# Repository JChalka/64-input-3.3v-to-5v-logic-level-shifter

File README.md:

# 64 input 3.3v to 5v logic level shifter
 Level shifter used to bring 3.3v logic to 5v logic using 4 SN74ALVC164245

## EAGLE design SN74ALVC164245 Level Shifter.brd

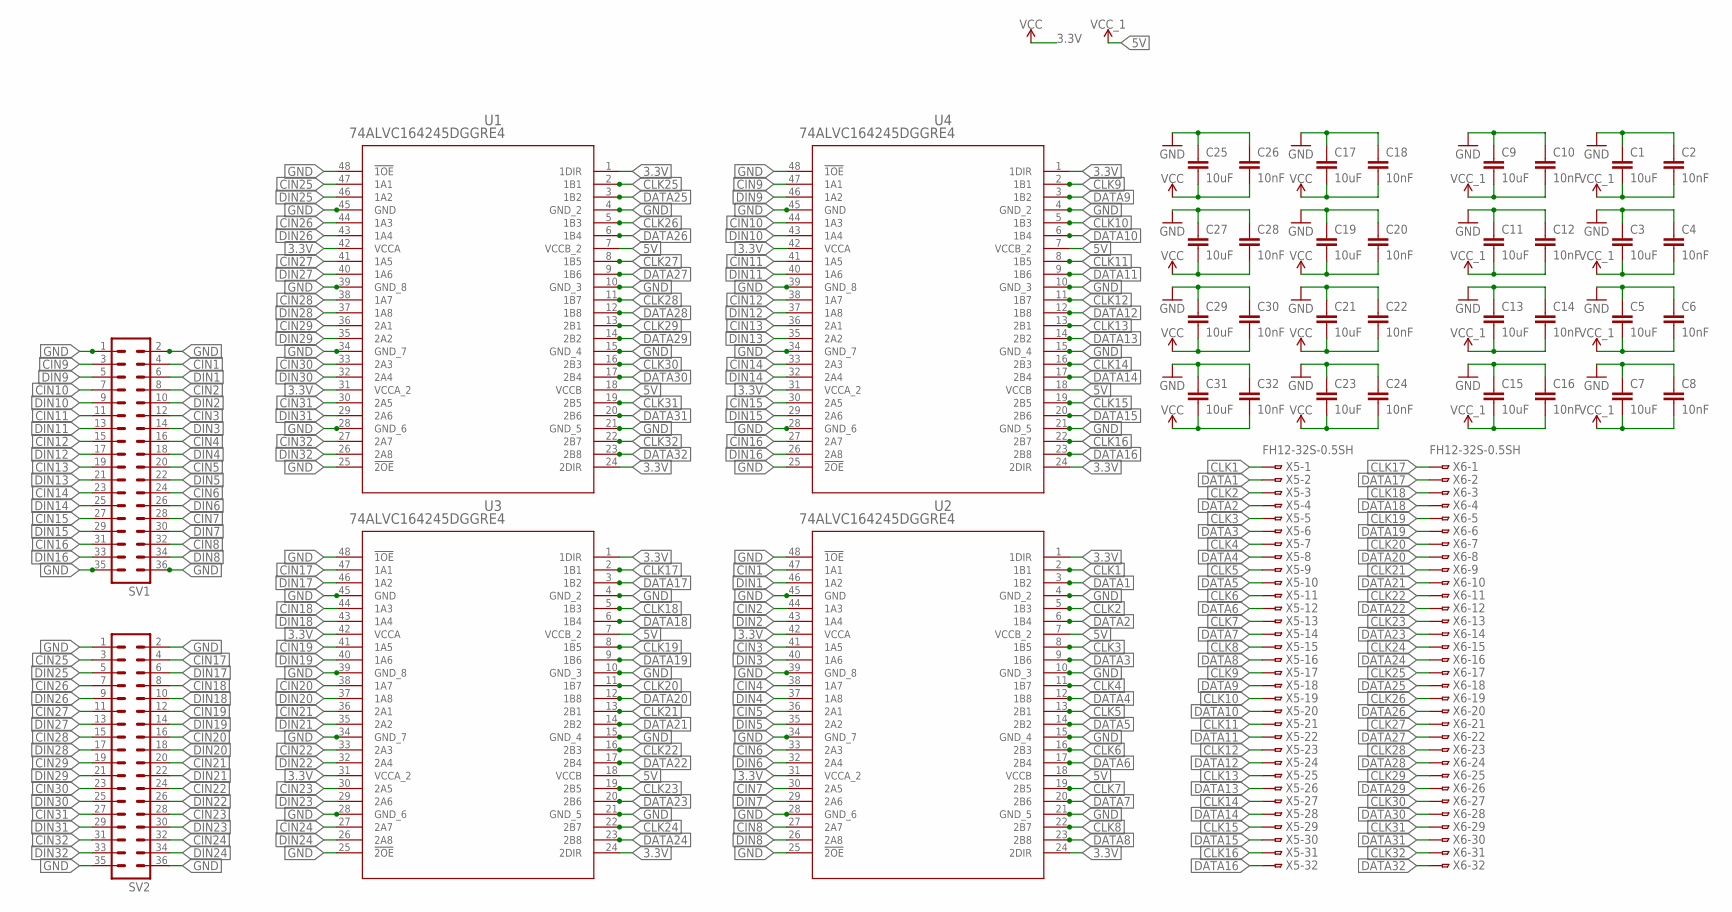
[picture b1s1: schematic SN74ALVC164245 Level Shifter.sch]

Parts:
C1, C3, C5, C7, C9, C11, C13, C15, C17, C19, C21, C23, C25, C27, C29, C31: 10uF; 0402-TIGHT
C2, C4, C6, C8, C10, C12, C14, C16, C18, C20, C22, C24, C26, C28, C30, C32: 10nF; 0402-TIGHT
SV1, SV2: MA18-2
U1, U2, U3, U4: 74ALVC164245DGGRE4; DGG48
X5, X6: FH12-32S-0.5SH

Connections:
3.3V: C17.2, C18.2, C19.2, C20.2, C21.2, C22.2, C23.2, C24.2, C25.2, C26.2, C27.2, C28.2, C29.2, C30.2, C31.2, C32.2, U1.1 (1DIR), U1.24 (2DIR), U1.31 (VCCA_2), U1.42 (VCCA), U2.1 (1DIR), U2.24 (2DIR), U2.31 (VCCA_2), U2.42 (VCCA), U3.1 (1DIR), U3.24 (2DIR), U3.31 (VCCA_2), U3.42 (VCCA), U4.1 (1DIR), U4.24 (2DIR), U4.31 (VCCA_2), U4.42 (VCCA)
5V: C1.2, C2.2, C3.2, C4.2, C5.2, C6.2, C7.2, C8.2, C9.2, C10.2, C11.2, C12.2, C13.2, C14.2, C15.2, C16.2, U1.7 (VCCB_2), U1.18 (VCCB), U2.7 (VCCB_2), U2.18 (VCCB), U3.7 (VCCB_2), U3.18 (VCCB), U4.7 (VCCB_2), U4.18 (VCCB)
CIN1: SV1.4, U2.47 (1A1)
CIN2: SV1.8, U2.44 (1A3)
CIN3: SV1.12, U2.41 (1A5)
CIN4: SV1.16, U2.38 (1A7)
CIN5: SV1.20, U2.36 (2A1)
CIN6: SV1.24, U2.33 (2A3)
CIN7: SV1.28, U2.30 (2A5)
CIN8: SV1.32, U2.27 (2A7)
CIN9: SV1.3, U4.47 (1A1)
CIN10: SV1.7, U4.44 (1A3)
CIN11: SV1.11, U4.41 (1A5)
CIN12: SV1.15, U4.38 (1A7)
CIN13: SV1.19, U4.36 (2A1)
CIN14: SV1.23, U4.33 (2A3)
CIN15: SV1.27, U4.30 (2A5)
CIN16: SV1.31, U4.27 (2A7)
CIN17: SV2.4, U3.47 (1A1)
CIN18: SV2.8, U3.44 (1A3)
CIN19: SV2.12, U3.41 (1A5)
CIN20: SV2.16, U3.38 (1A7)
CIN21: SV2.20, U3.36 (2A1)
CIN22: SV2.24, U3.33 (2A3)
CIN23: SV2.28, U3.30 (2A5)
CIN24: SV2.32, U3.27 (2A7)
CIN25: SV2.3, U1.47 (1A1)
CIN26: SV2.7, U1.44 (1A3)
CIN27: SV2.11, U1.41 (1A5)
CIN28: SV2.15, U1.38 (1A7)
CIN29: SV2.19, U1.36 (2A1)
CIN30: SV2.23, U1.33 (2A3)
CIN31: SV2.27, U1.30 (2A5)
CIN32: SV2.31, U1.27 (2A7)
CLK1: U2.2 (1B1), X5.1
CLK2: U2.5 (1B3), X5.3
CLK3: U2.8 (1B5), X5.5
CLK4: U2.11 (1B7), X5.7
CLK5: U2.13 (2B1), X5.9
CLK6: U2.16 (2B3), X5.11
CLK7: U2.19 (2B5), X5.13
CLK8: U2.22 (2B7), X5.15
CLK9: U4.2 (1B1), X5.17
CLK10: U4.5 (1B3), X5.19
CLK11: U4.8 (1B5), X5.21
CLK12: U4.11 (1B7), X5.23
CLK13: U4.13 (2B1), X5.25
CLK14: U4.16 (2B3), X5.27
CLK15: U4.19 (2B5), X5.29
CLK16: U4.22 (2B7), X5.31
CLK17: U3.2 (1B1), X6.1
CLK18: U3.5 (1B3), X6.3
CLK19: U3.8 (1B5), X6.5
CLK20: U3.11 (1B7), X6.7
CLK21: U3.13 (2B1), X6.9
CLK22: U3.16 (2B3), X6.11
CLK23: U3.19 (2B5), X6.13
CLK24: U3.22 (2B7), X6.15
CLK25: U1.2 (1B1), X6.17
CLK26: U1.5 (1B3), X6.19
CLK27: U1.8 (1B5), X6.21
CLK28: U1.11 (1B7), X6.23
CLK29: U1.13 (2B1), X6.25
CLK30: U1.16 (2B3), X6.27
CLK31: U1.19 (2B5), X6.29
CLK32: U1.22 (2B7), X6.31
DATA1: U2.3 (1B2), X5.2
DATA2: U2.6 (1B4), X5.4
DATA3: U2.9 (1B6), X5.6
DATA4: U2.12 (1B8), X5.8
DATA5: U2.14 (2B2), X5.10
DATA6: U2.17 (2B4), X5.12
DATA7: U2.20 (2B6), X5.14
DATA8: U2.23 (2B8), X5.16
DATA9: U4.3 (1B2), X5.18
DATA10: U4.6 (1B4), X5.20
DATA11: U4.9 (1B6), X5.22
DATA12: U4.12 (1B8), X5.24
DATA13: U4.14 (2B2), X5.26
DATA14: U4.17 (2B4), X5.28
DATA15: U4.20 (2B6), X5.30
DATA16: U4.23 (2B8), X5.32
DATA17: U3.3 (1B2), X6.2
DATA18: U3.6 (1B4), X6.4
DATA19: U3.9 (1B6), X6.6
DATA20: U3.12 (1B8), X6.8
DATA21: U3.14 (2B2), X6.10
DATA22: U3.17 (2B4), X6.12
DATA23: U3.20 (2B6), X6.14
DATA24: U3.23 (2B8), X6.16
DATA25: U1.3 (1B2), X6.18
DATA26: U1.6 (1B4), X6.20
DATA27: U1.9 (1B6), X6.22
DATA28: U1.12 (1B8), X6.24
DATA29: U1.14 (2B2), X6.26
DATA30: U1.17 (2B4), X6.28
DATA31: U1.20 (2B6), X6.30
DATA32: U1.23 (2B8), X6.32
DIN1: SV1.6, U2.46 (1A2)
DIN2: SV1.10, U2.43 (1A4)
DIN3: SV1.14, U2.40 (1A6)
DIN4: SV1.18, U2.37 (1A8)
DIN5: SV1.22, U2.35 (2A2)
DIN6: SV1.26, U2.32 (2A4)
DIN7: SV1.30, U2.29 (2A6)
DIN8: SV1.34, U2.26 (2A8)
DIN9: SV1.5, U4.46 (1A2)
DIN10: SV1.9, U4.43 (1A4)
DIN11: SV1.13, U4.40 (1A6)
DIN12: SV1.17, U4.37 (1A8)
DIN13: SV1.21, U4.35 (2A2)
DIN14: SV1.25, U4.32 (2A4)
DIN15: SV1.29, U4.29 (2A6)
DIN16: SV1.33, U4.26 (2A8)
DIN17: SV2.6, U3.46 (1A2)
DIN18: SV2.10, U3.43 (1A4)
DIN19: SV2.14, U3.40 (1A6)
DIN20: SV2.18, U3.37 (1A8)
DIN21: SV2.22, U3.35 (2A2)
DIN22: SV2.26, U3.32 (2A4)
DIN23: SV2.30, U3.29 (2A6)
DIN24: SV2.34, U3.26 (2A8)
DIN25: SV2.5, U1.46 (1A2)
DIN26: SV2.9, U1.43 (1A4)
DIN27: SV2.13, U1.40 (1A6)
DIN28: SV2.17, U1.37 (1A8)
DIN29: SV2.21, U1.35 (2A2)
DIN30: SV2.25, U1.32 (2A4)
DIN31: SV2.29, U1.29 (2A6)
DIN32: SV2.33, U1.26 (2A8)
GND: C1.1, C2.1, C3.1, C4.1, C5.1, C6.1, C7.1, C8.1, C9.1, C10.1, C11.1, C12.1, C13.1, C14.1, C15.1, C16.1, C17.1, C18.1, C19.1, C20.1, C21.1, C22.1, C23.1, C24.1, C25.1, C26.1, C27.1, C28.1, C29.1, C30.1, C31.1, C32.1, SV1.1, SV1.2, SV1.35, SV1.36, SV2.1, SV2.2, SV2.35, SV2.36, U1.4 (GND_2), U1.10 (GND_3), U1.15 (GND_4), U1.21 (GND_5), U1.25 (!2OE), U1.28 (GND_6), U1.34 (GND_7), U1.39 (GND_8), U1.45 (GND), U1.48 (!1OE), U2.4 (GND_2), U2.10 (GND_3), U2.15 (GND_4), U2.21 (GND_5), U2.25 (!2OE), U2.28 (GND_6), U2.34 (GND_7), U2.39 (GND_8), U2.45 (GND), U2.48 (!1OE), U3.4 (GND_2), U3.10 (GND_3), U3.15 (GND_4), U3.21 (GND_5), U3.25 (!2OE), U3.28 (GND_6), U3.34 (GND_7), U3.39 (GND_8), U3.45 (GND), U3.48 (!1OE), U4.4 (GND_2), U4.10 (GND_3), U4.15 (GND_4), U4.21 (GND_5), U4.25 (!2OE), U4.28 (GND_6), U4.34 (GND_7), U4.39 (GND_8), U4.45 (GND), U4.48 (!1OE)

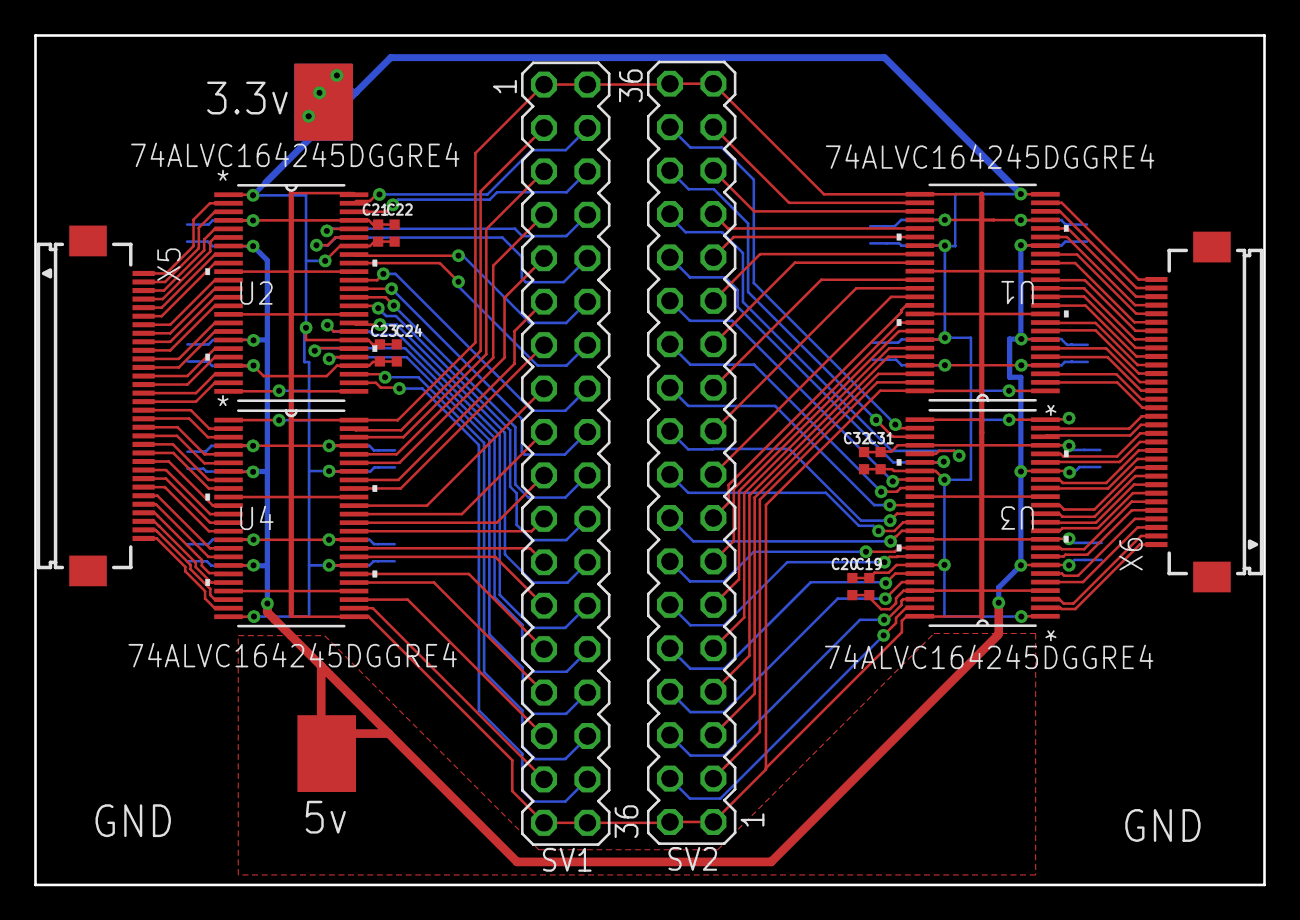
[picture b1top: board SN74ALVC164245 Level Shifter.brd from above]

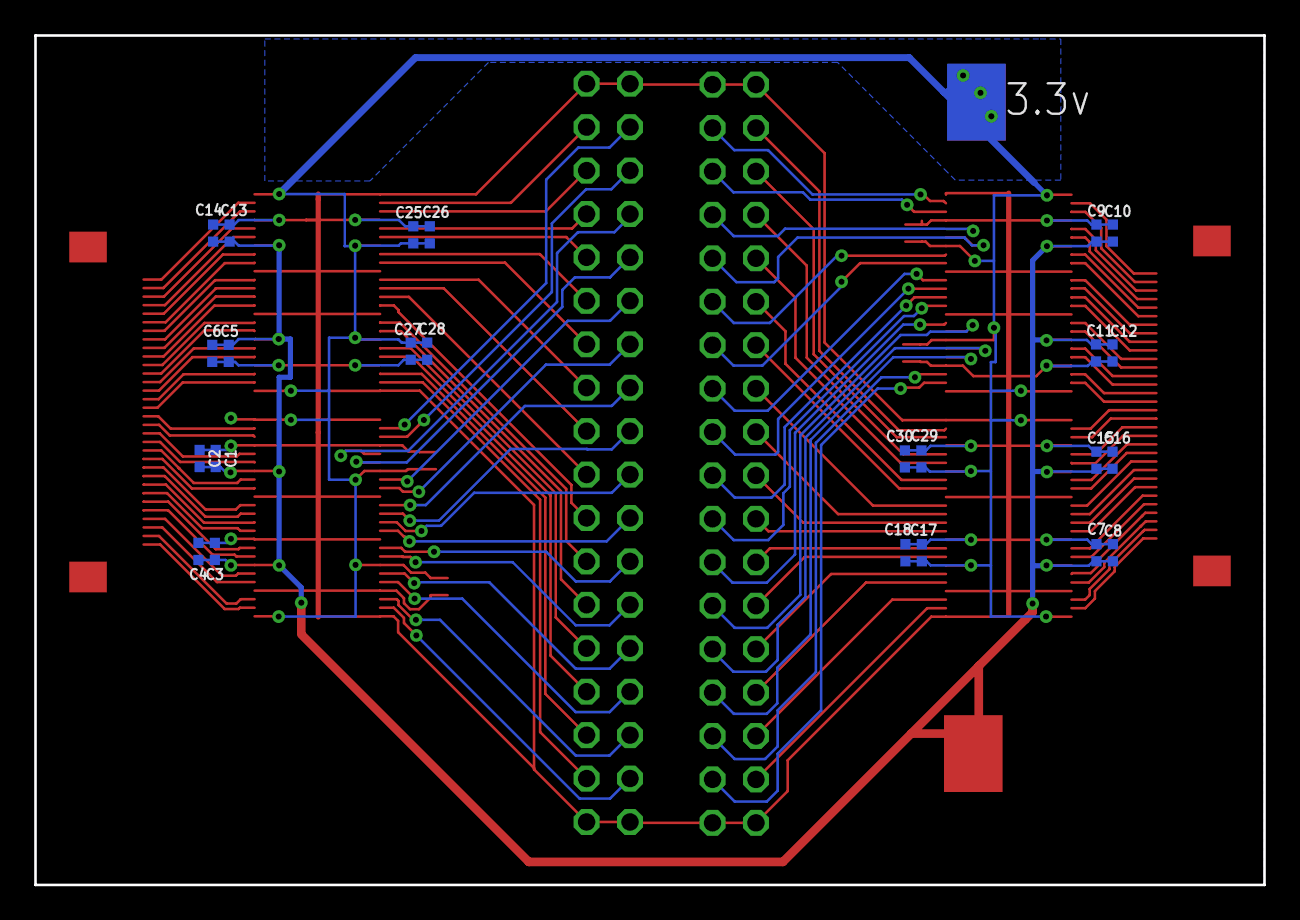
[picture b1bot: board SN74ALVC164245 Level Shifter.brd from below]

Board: 2 copper layers, 71.9 x 49.7 mm, 40 parts (24 on the bottom side), 131 nets.

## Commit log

2021-04-28 Initial Commit
    Added V1 Gerber, PCB, and Schematic files as well as the needed libraries
2021-04-28 Create LICENSE

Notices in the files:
parts and their libraries:
SparkFun-Capacitors: Licensing: Creative Commons ShareAlike 4.0 International - https://creativecommons.org/licenses/by-sa/4.0
